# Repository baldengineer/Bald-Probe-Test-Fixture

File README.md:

Test fixture to see response of an oscilloscope probe when stimulated with a high-frequency edge.

## Parts list
- Edge Launch SMA Connector (TBD)
- [PCB](hardware/)

## Status: Work In Progress
Rev 1 sent to fab

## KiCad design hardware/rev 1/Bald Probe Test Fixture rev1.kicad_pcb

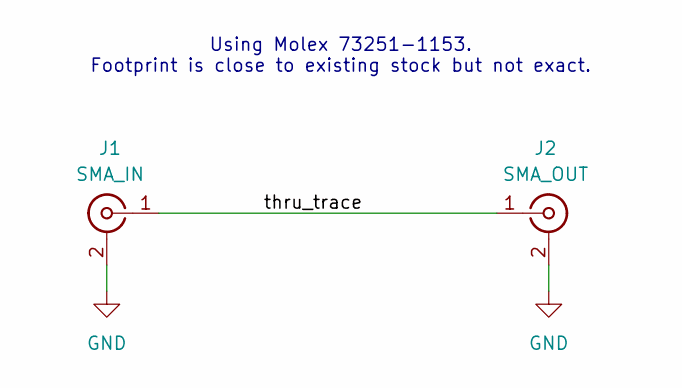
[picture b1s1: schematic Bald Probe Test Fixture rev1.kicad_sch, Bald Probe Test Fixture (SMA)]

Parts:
J1: SMA_IN; SMA_Molex_73251-1153_EdgeMount_Horizontal
J2: SMA_OUT; SMA_Molex_73251-1153_EdgeMount_Horizontal

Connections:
/thru_trace: J1.1 (In), J2.1 (In)
GND: J1.2 (Ext), J2.2 (Ext)

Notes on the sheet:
Using Molex 73251-1153. Footprint is close to existing stock but not exact.

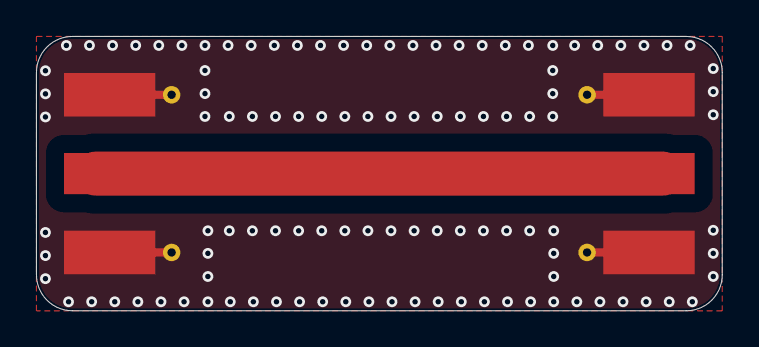
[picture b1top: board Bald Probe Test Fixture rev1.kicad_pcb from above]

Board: 2 copper layers, 38.1 x 15.2 mm, 3 parts (1 on the bottom side), 2 nets.

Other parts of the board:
kibuzzard-66881A8D: G***; kibuzzard-66881A8D

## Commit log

2024-07-05 schematic and pcb. need to setup board rules
2024-07-05 added lck file
2024-07-05 added oshpark 4-layer stackup details
2024-07-05 ignoring step exports (just used for visual checks)
2024-07-05 changed to oshpark after dark (2-layer)
2024-07-05 ignore artwork, feeling dumb, might delete later
2024-07-05 rev1 ready for fab
2024-07-05 ignore zips
2024-07-05 added image to readme
2024-08-01 prep rev2
